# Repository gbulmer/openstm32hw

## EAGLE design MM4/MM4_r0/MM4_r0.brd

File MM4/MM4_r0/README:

This design is a clone of Leaf Labs Maple Mini board (called MM4) with the following variations
	from the original:

	- 0.8 inch pitch between connectors rather than 0.6". This means dual rows of 
		sip connectors are required rather than a 40 pin dip (a socket layout can 
		easily be defined for either LeafLabs or MM4 using 3 sip connectors.)

	- identical pin functions except for the above mentioned pitch change.

	- two layer layout in Eagle which can be modified with the free version of 
		Eagle (original was done with Eagle v6.1). Ground planes that are 
		as large as practical are used given the two layer constraint (modification 
		to internal power/ground planes is, of course, fairly straightforward, 
		but requires the much more expensive Eagle license).

	- 64 pin processor that can be STM32F10xC/D/E orSTM32F4 or STM32L1 series. This means 
		the F1 chip variants with larger memories can be used or the L1 low power series 
		(F1 and L1 require two solder bridge jumpers to be installed), or the faster Cortex-M4 F4 series.

	- considerably less detailed top silkscreen layer in this version of MM4.

	- The USB termination function has been re-implemented with a dedicated USB terminator
		chip that contains the termination resistors and the signalling resistor to
		describe the board to an up-stream host as a full speed USB peripheral.
		The disconnect function is then separately implemented with an open collector 
		inverter. The original implemented the signalling and disconnect via a 
		transistor/resistor network.

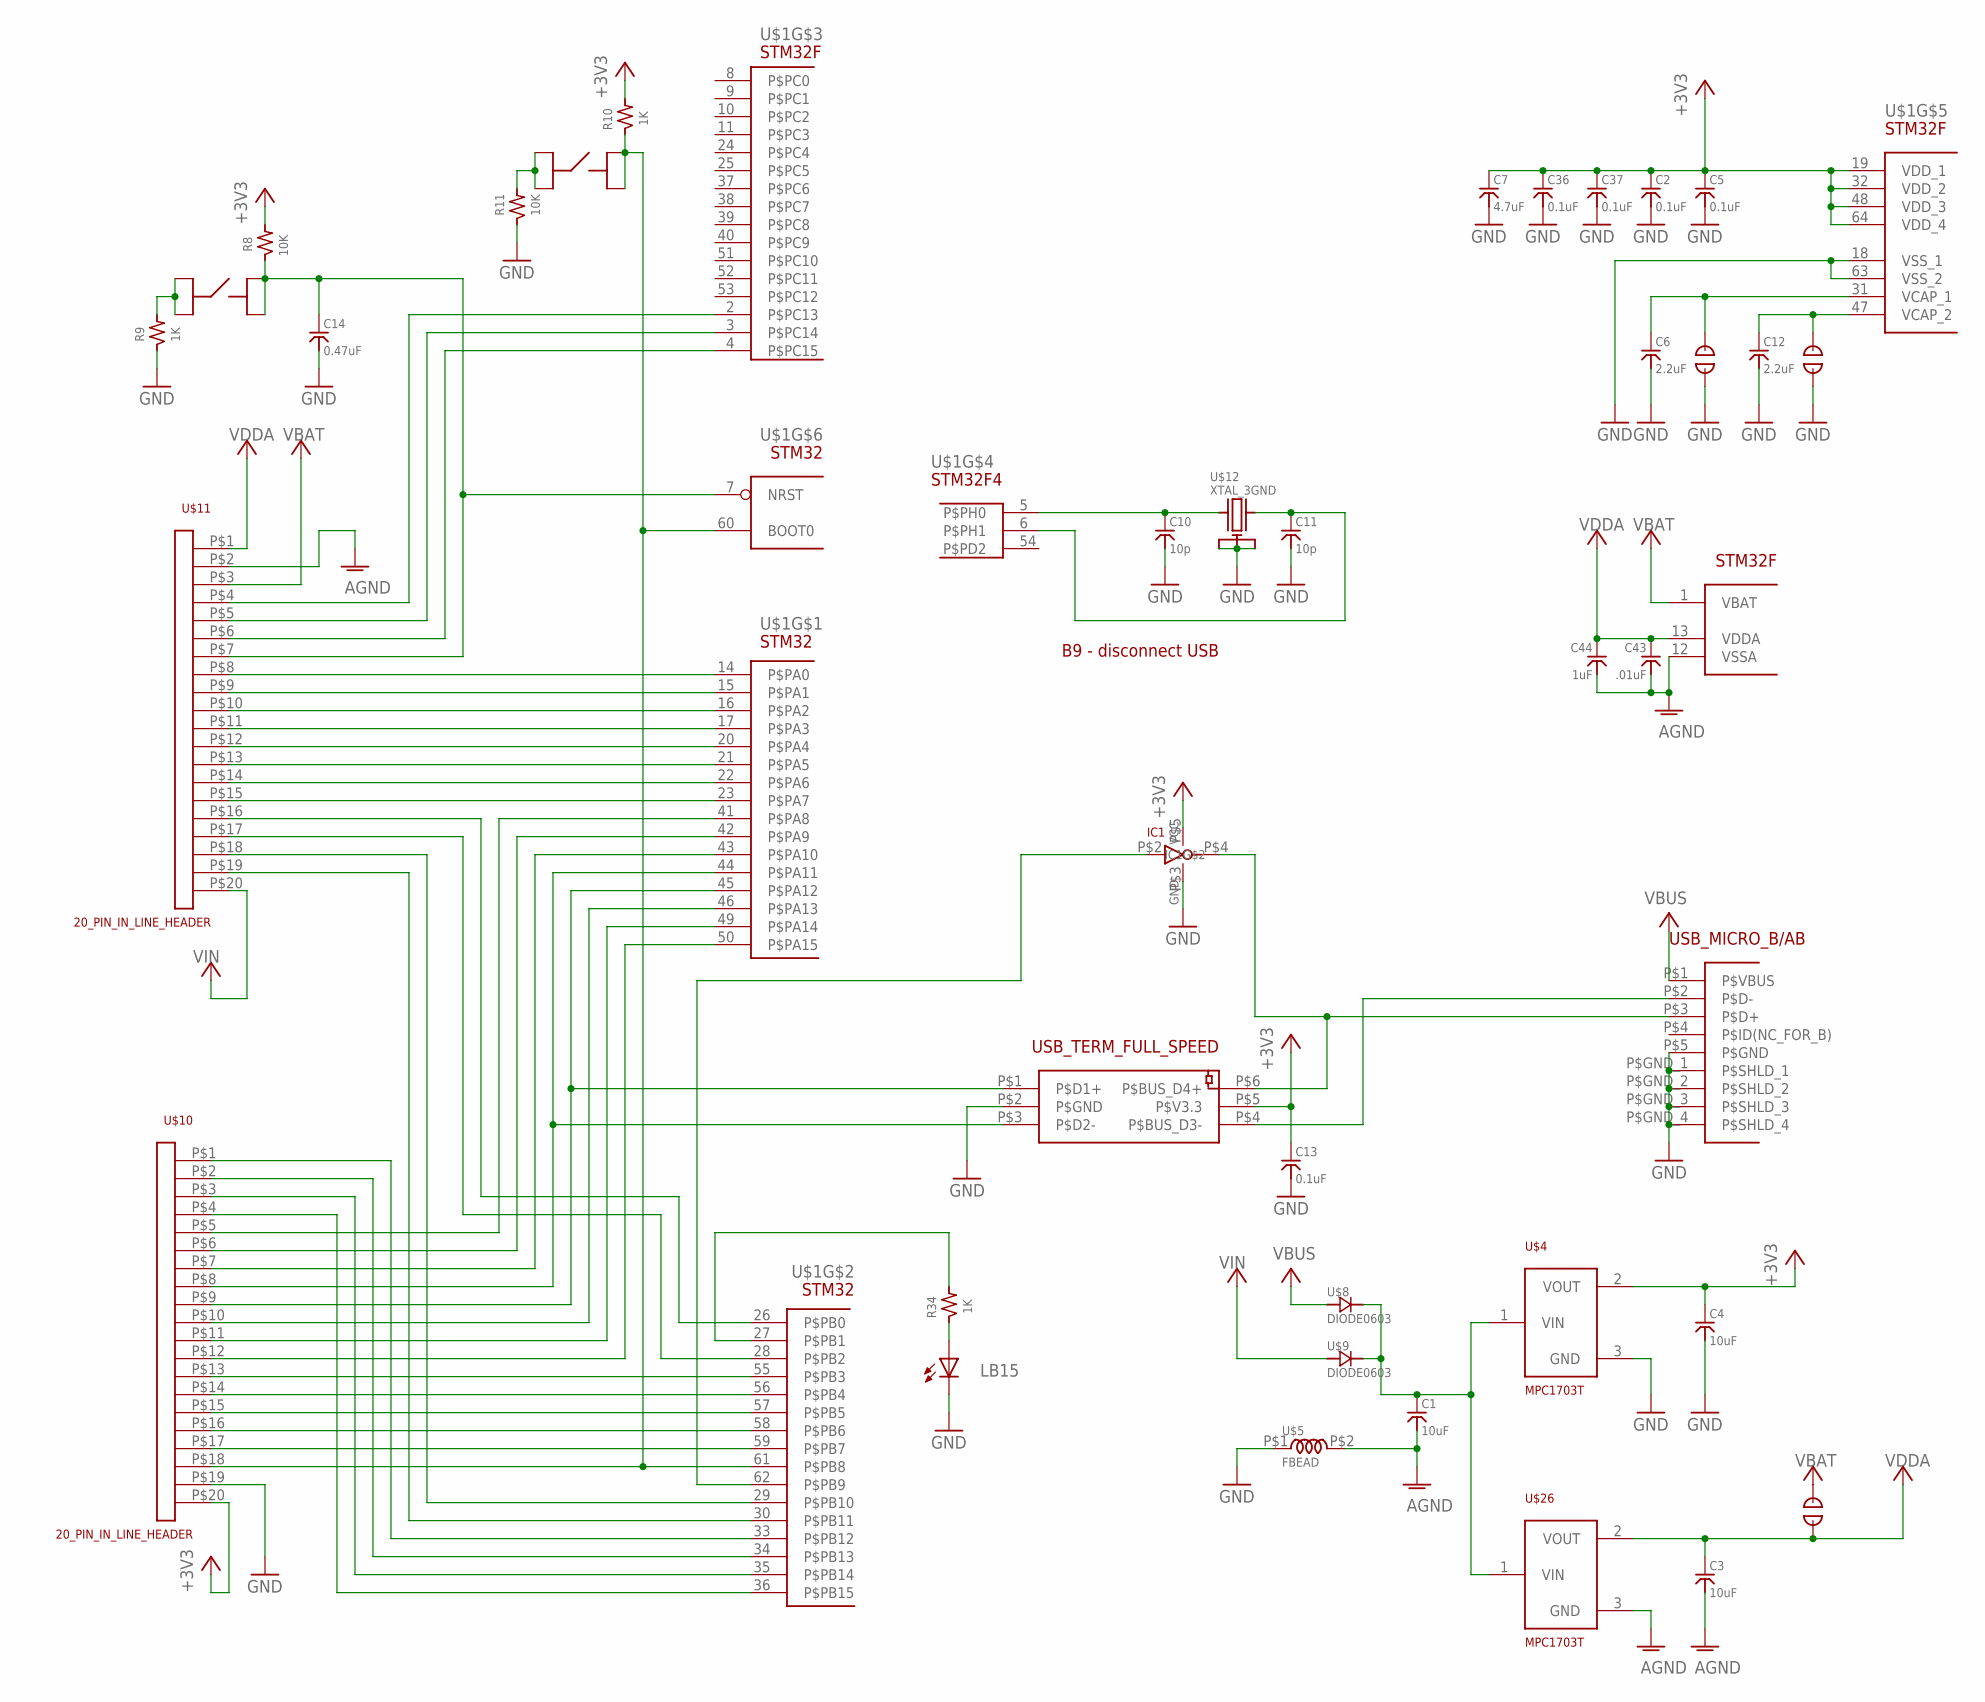
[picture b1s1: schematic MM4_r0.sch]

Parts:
C1, C3, C4: 10uF; 0603
C2, C5, C13, C36, C37: 0.1uF; 0603
C6, C12: 2.2uF; 0603
C7: 4.7uF; 0603
C10, C11: 10p; 0603
C14: 0.47uF; 0603
C43: .01uF; 0603
C44: 1uF; 0603
IC1: 7SZ05; SC-70-5
LB15: LED_CMD280603+; 0603+
R8, R11: 10K; 0603
R9, R10, R34: 1K; 0603
U$1: STM32F40XRG; TQFP64
U$2, U$3, U$13: JUMPER_SOLDER; JUMPER
U$4, U$26: MPC1703T; SOT23-3
U$5: FBEAD; BEAD_0603
U$8, U$9: DIODE0603; 0603_DIODE
U$10, U$11: 20_PIN_IN_LINE_HEADER; 20_PIN_IN_LINE
U$12: XTAL_3GND; XTAL=TXC7M-3
U$14: MICRO_USB_B; USB-ZX-62-B-5PA
U$23: USB_TERM_FS; SOT-666IP
U$24, U$25: SW_SMD_TACTILE

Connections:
+3V3: C2.P$1, C4.P$1, C5.P$1, C7.P$1, C13.P$1, C36.P$1, C37.P$1, IC1.P$5 (VCC), R8.P$1, R10.P$1, U$1.19 (VDD_1), U$1.32 (VDD_2), U$1.48 (VDD_3), U$1.64 (VDD_4), U$4.2 (VOUT), U$10.P$20, U$23.P$5 (P$V3.3)
AGND: C1.P$2, C3.P$2, C43.P$2, C44.P$2, U$1.12 (VSSA), U$5.P$2, U$11.P$2, U$26.3 (GND)
GND: C2.P$2, C4.P$2, C5.P$2, C6.P$2, C7.P$2, C10.P$2, C11.P$2, C12.P$2, C13.P$2, C14.P$2, C36.P$2, C37.P$2, IC1.P$3 (GND), LB15.P$2- (C), R9.P$2, R11.P$2, U$1.18 (VSS_1), U$1.63 (VSS_2), U$2.P$1, U$3.P$1, U$4.3 (GND), U$5.P$1, U$10.P$19, U$12.GND (P$GND_1), U$12.P$2 (P$GND_2), U$12.P$4 (P$GND_3), U$14.P$5 (P$GND), U$14.P$GND_1 (P$SHLD_1), U$14.P$GND_2 (P$SHLD_2), U$14.P$GND_3 (P$SHLD_3), U$14.P$GND_4 (P$SHLD_4), U$23.P$2 (P$GND)
unnamed: C10.P$1, U$1.5 (P$PH0), U$12.P$1 (P$XT1)
unnamed: LB15.P$1+ (A), R34.P$2
unnamed: C11.P$1, U$1.6 (P$PH1), U$12.P$3 (P$XT2)
unnamed: U$1.14 (P$PA0), U$11.P$8
unnamed: U$1.15 (P$PA1), U$11.P$9
unnamed: U$1.2 (P$PC13), U$11.P$4
unnamed: R34.P$1, U$1.27 (P$PB1)
unnamed: U$14.P$2 (P$D-), U$23.P$4 (P$BUS_D3-)
unnamed: U$1.16 (P$PA2), U$11.P$10
unnamed: U$1.17 (P$PA3), U$11.P$11
unnamed: U$1.20 (P$PA4), U$11.P$12
unnamed: U$1.21 (P$PA5), U$11.P$13
unnamed: U$1.22 (P$PA6), U$11.P$14
unnamed: U$1.23 (P$PA7), U$11.P$15
unnamed: U$1.26 (P$PB0), U$11.P$16
unnamed: U$1.28 (P$PB2), U$11.P$17
unnamed: U$1.29 (P$PB10), U$11.P$18
unnamed: IC1.P$4 (P$OUT), U$14.P$3 (P$D+), U$23.P$6 (P$BUS_D4+)
unnamed: U$1.30 (P$PB11), U$11.P$19
unnamed: U$1.33 (P$PB12), U$10.P$1
unnamed: U$1.34 (P$PB13), U$10.P$2
unnamed: U$1.35 (P$PB14), U$10.P$3
unnamed: U$1.36 (P$PB15), U$10.P$4
unnamed: U$1.41 (P$PA8), U$10.P$5
unnamed: U$1.42 (P$PA9), U$10.P$6
unnamed: U$1.43 (P$PA10), U$10.P$7
unnamed: U$1.44 (P$PA11), U$10.P$8, U$23.P$3 (P$D2-)
unnamed: U$1.45 (P$PA12), U$10.P$9, U$23.P$1 (P$D1+)
unnamed: U$1.46 (P$PA13), U$10.P$10
unnamed: U$1.49 (P$PA14), U$10.P$11
unnamed: U$1.50 (P$PA15), U$10.P$12
unnamed: U$1.55 (P$PB3), U$10.P$13
unnamed: U$1.56 (P$PB4), U$10.P$14
unnamed: U$1.57 (P$PB5), U$10.P$15
unnamed: U$1.58 (P$PB6), U$10.P$16
unnamed: U$1.59 (P$PB7), U$10.P$17
unnamed: R10.P$2, U$1.60 (BOOT0), U$1.61 (P$PB8), U$10.P$18, U$24.P$3, U$24.P$4
unnamed: IC1.P$2 (P$IN), U$1.62 (P$PB9)
unnamed: R9.P$1, U$25.P$1, U$25.P$2
unnamed: C14.P$1, R8.P$2, U$1.7 (NRST), U$11.P$7, U$25.P$3, U$25.P$4
unnamed: R11.P$1, U$24.P$1, U$24.P$2
unnamed: C1.P$1, U$4.1 (VIN), U$8.P$2, U$9.P$2, U$26.1 (VIN)
unnamed: U$1.3 (P$PC14), U$11.P$5
unnamed: C6.P$1, U$1.31 (VCAP_1), U$2.P$2
unnamed: C12.P$1, U$1.47 (VCAP_2), U$3.P$2
unnamed: U$1.4 (P$PC15), U$11.P$6
VBAT: U$1.1 (VBAT), U$11.P$3, U$13.P$2
VBUS: U$8.P$1, U$14.P$1 (P$VBUS)
VDDA: C3.P$1, C43.P$1, C44.P$1, U$1.13 (VDDA), U$11.P$1, U$13.P$1, U$26.2 (VOUT)
VIN: U$9.P$1, U$11.P$20

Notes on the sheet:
B9 - disconnect USB

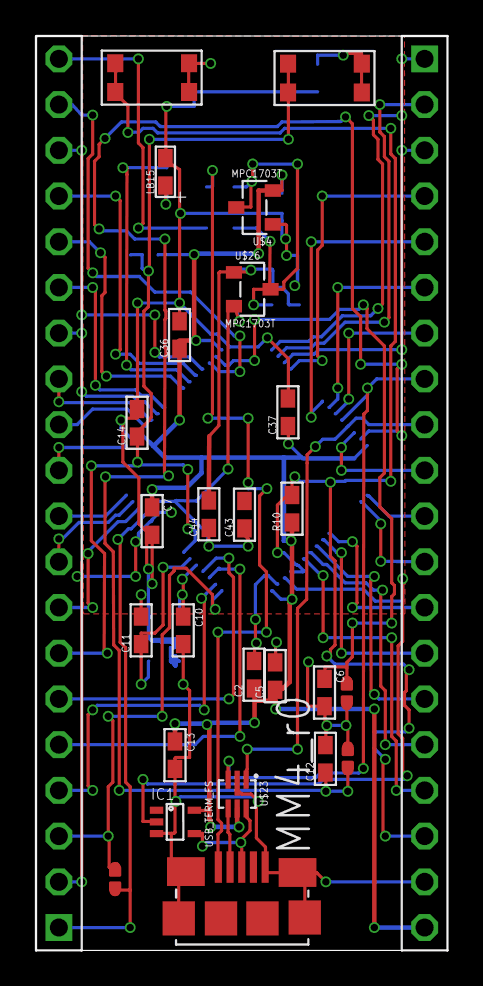
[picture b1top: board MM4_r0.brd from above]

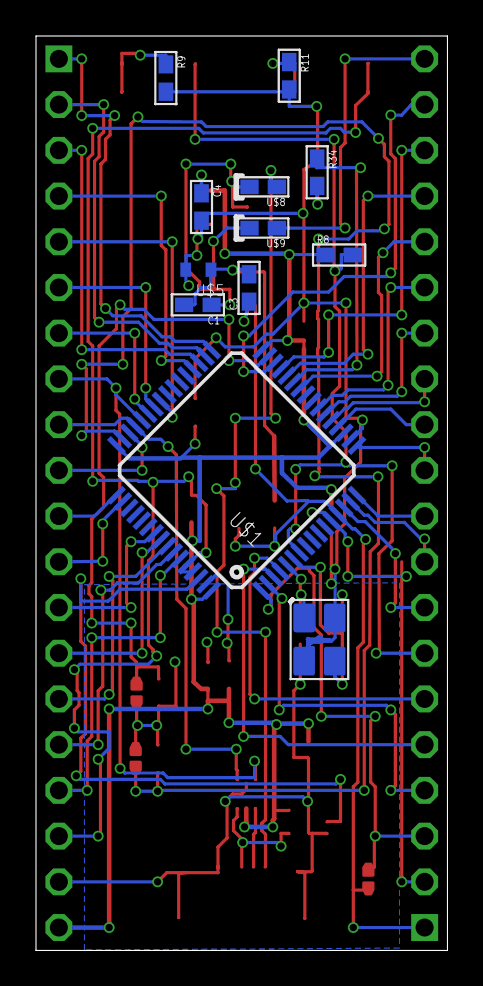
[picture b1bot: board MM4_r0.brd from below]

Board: 2 copper layers, 22.9 x 50.8 mm, 39 parts (13 on the bottom side), 53 nets.
